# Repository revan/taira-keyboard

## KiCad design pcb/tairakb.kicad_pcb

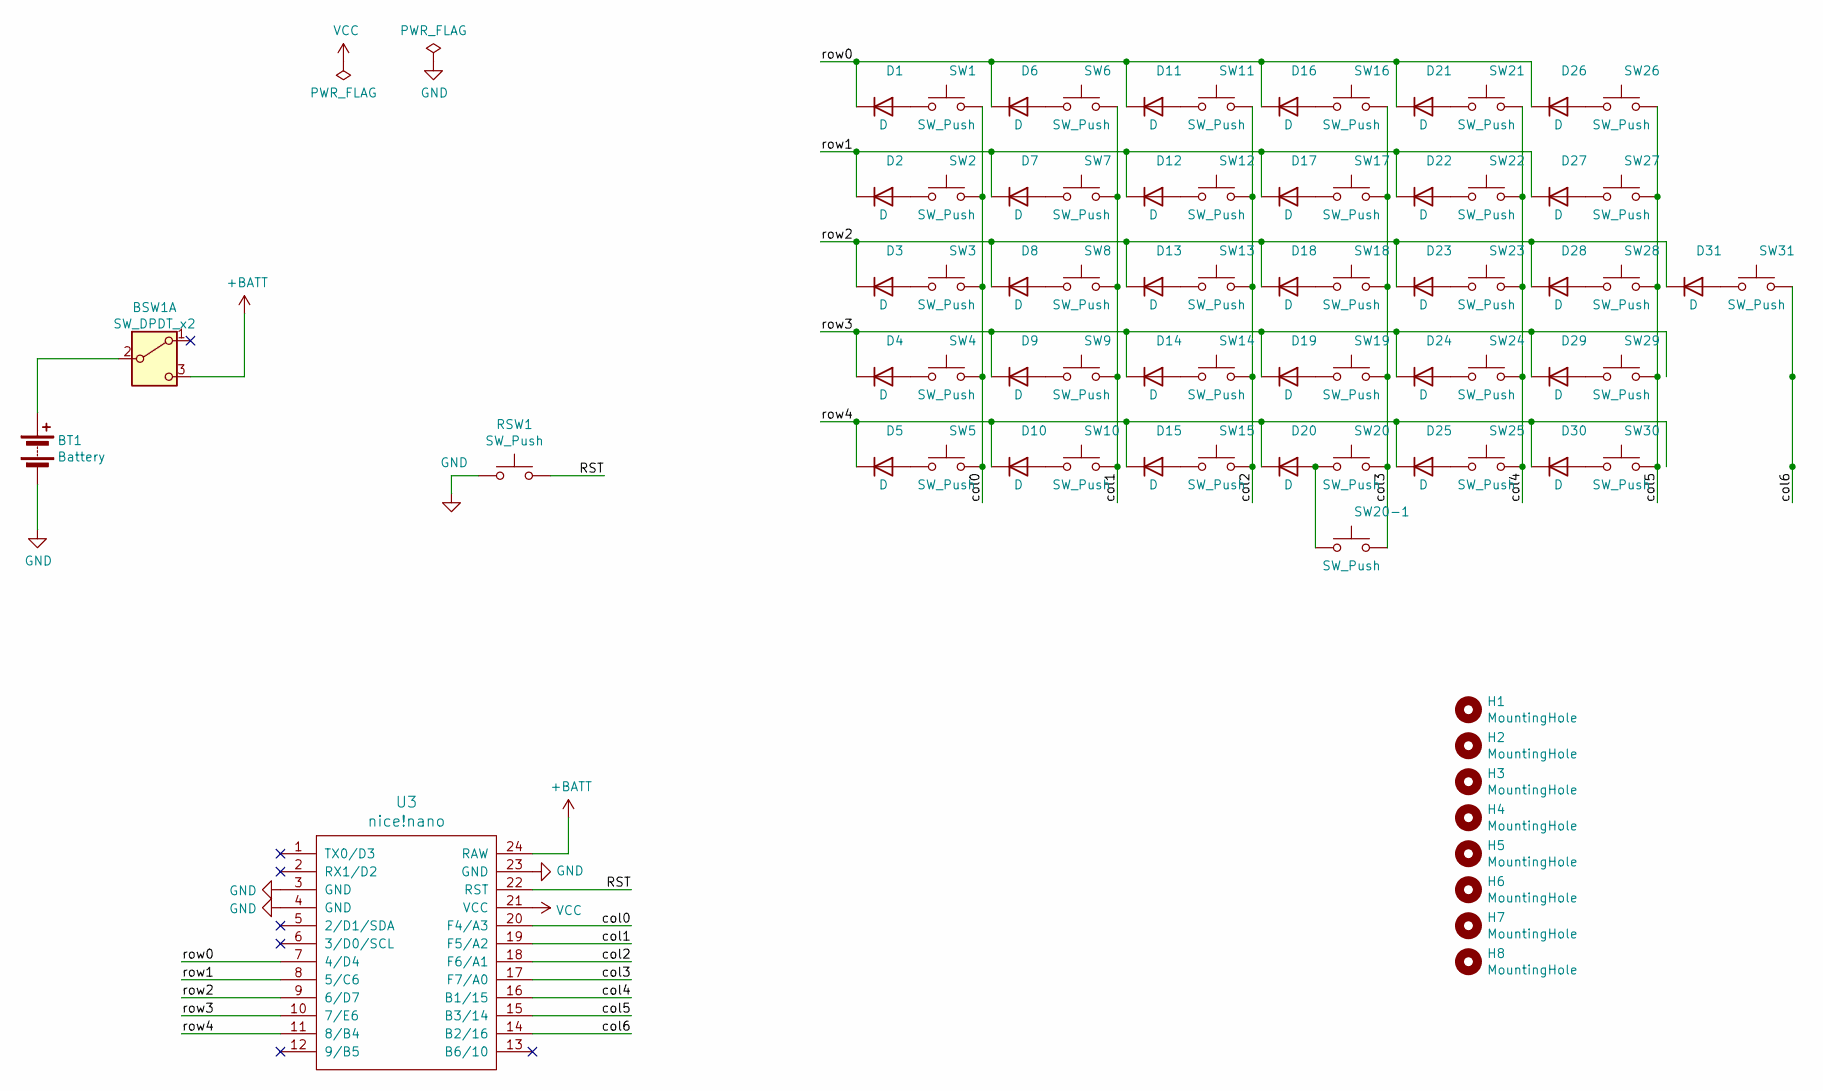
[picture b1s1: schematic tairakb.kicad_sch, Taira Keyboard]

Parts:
BSW1: SW_DPDT_x2; SS-12D00
BT1: Battery; Battery_Wire_Connector
D1, D2, D3, D4, D5, D6, D7, D8, D9, D10, D11, D12, D13, D14, D15, D16, D17, D18, D19, D20, D21, D22, D23, D24, D25, D26, D27, D28, D29, D30, D31: D; D3_SMD
H1, H2, H3, H4, H5, H6, H7, H8: MountingHole; LEGO_HOLE
RSW1: SW_Push; ResetSW
SW1, SW2, SW3, SW4, SW5, SW6, SW7, SW8, SW9, SW10, SW11, SW12, SW13, SW14, SW15, SW16, SW17, SW18, SW19, SW20, SW20-1, SW21, SW22, SW23, SW24, SW25, SW26, SW27, SW28, SW29, SW31: SW_Push; Choc_Hotswap
SW30: SW_Push; Choc_Hotswap_1.5U
U3: nice!nano; nicenano

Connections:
+BATT: BSW1.3 (C), U3.24 (RAW)
/RST: RSW1.2, U3.22 (RST)
/col0: SW1.2, SW2.2, SW3.2, SW4.2, SW5.2, U3.20 (F4/A3)
/col1: SW6.2, SW7.2, SW8.2, SW9.2, SW10.2, U3.19 (F5/A2)
/col2: SW11.2, SW12.2, SW13.2, SW14.2, SW15.2, U3.18 (F6/A1)
/col3: SW16.2, SW17.2, SW18.2, SW19.2, SW20.2, SW20-1.2, U3.17 (F7/A0)
/col4: SW21.2, SW22.2, SW23.2, SW24.2, SW25.2, U3.16 (B1/15)
/col5: SW26.2, SW27.2, SW28.2, SW29.2, SW30.2, U3.15 (B3/14)
/col6: SW31.2, U3.14 (B2/16)
/row0: D1.1 (K), D6.1 (K), D11.1 (K), D16.1 (K), D21.1 (K), D26.1 (K), U3.7 (4/D4)
/row1: D2.1 (K), D7.1 (K), D12.1 (K), D17.1 (K), D22.1 (K), D27.1 (K), U3.8 (5/C6)
/row2: D3.1 (K), D8.1 (K), D13.1 (K), D18.1 (K), D23.1 (K), D28.1 (K), D31.1 (K), U3.9 (6/D7)
/row3: D4.1 (K), D9.1 (K), D14.1 (K), D19.1 (K), D24.1 (K), D29.1 (K), U3.10 (7/E6)
/row4: D5.1 (K), D10.1 (K), D15.1 (K), D20.1 (K), D25.1 (K), D30.1 (K), U3.11 (8/B4)
GND: BT1.2 (-), RSW1.1, U3.3 (GND), U3.4 (GND), U3.23 (GND)
unnamed: BSW1.2 (B), BT1.1 (+)
unnamed: D1.2 (A), SW1.1
unnamed: D2.2 (A), SW2.1
unnamed: D3.2 (A), SW3.1
unnamed: D4.2 (A), SW4.1
unnamed: D5.2 (A), SW5.1
unnamed: D6.2 (A), SW6.1
unnamed: D7.2 (A), SW7.1
unnamed: D8.2 (A), SW8.1
unnamed: D9.2 (A), SW9.1
unnamed: D10.2 (A), SW10.1
unnamed: D11.2 (A), SW11.1
unnamed: D12.2 (A), SW12.1
unnamed: D13.2 (A), SW13.1
unnamed: D14.2 (A), SW14.1
unnamed: D15.2 (A), SW15.1
unnamed: D16.2 (A), SW16.1
unnamed: D17.2 (A), SW17.1
unnamed: D18.2 (A), SW18.1
unnamed: D19.2 (A), SW19.1
unnamed: D20.2 (A), SW20.1, SW20-1.1
unnamed: D21.2 (A), SW21.1
unnamed: D22.2 (A), SW22.1
unnamed: D23.2 (A), SW23.1
unnamed: D24.2 (A), SW24.1
unnamed: D25.2 (A), SW25.1
unnamed: D26.2 (A), SW26.1
unnamed: D27.2 (A), SW27.1
unnamed: D28.2 (A), SW28.1
unnamed: D29.2 (A), SW29.1
unnamed: D30.2 (A), SW30.1
unnamed: D31.2 (A), SW31.1
VCC: U3.21 (VCC)

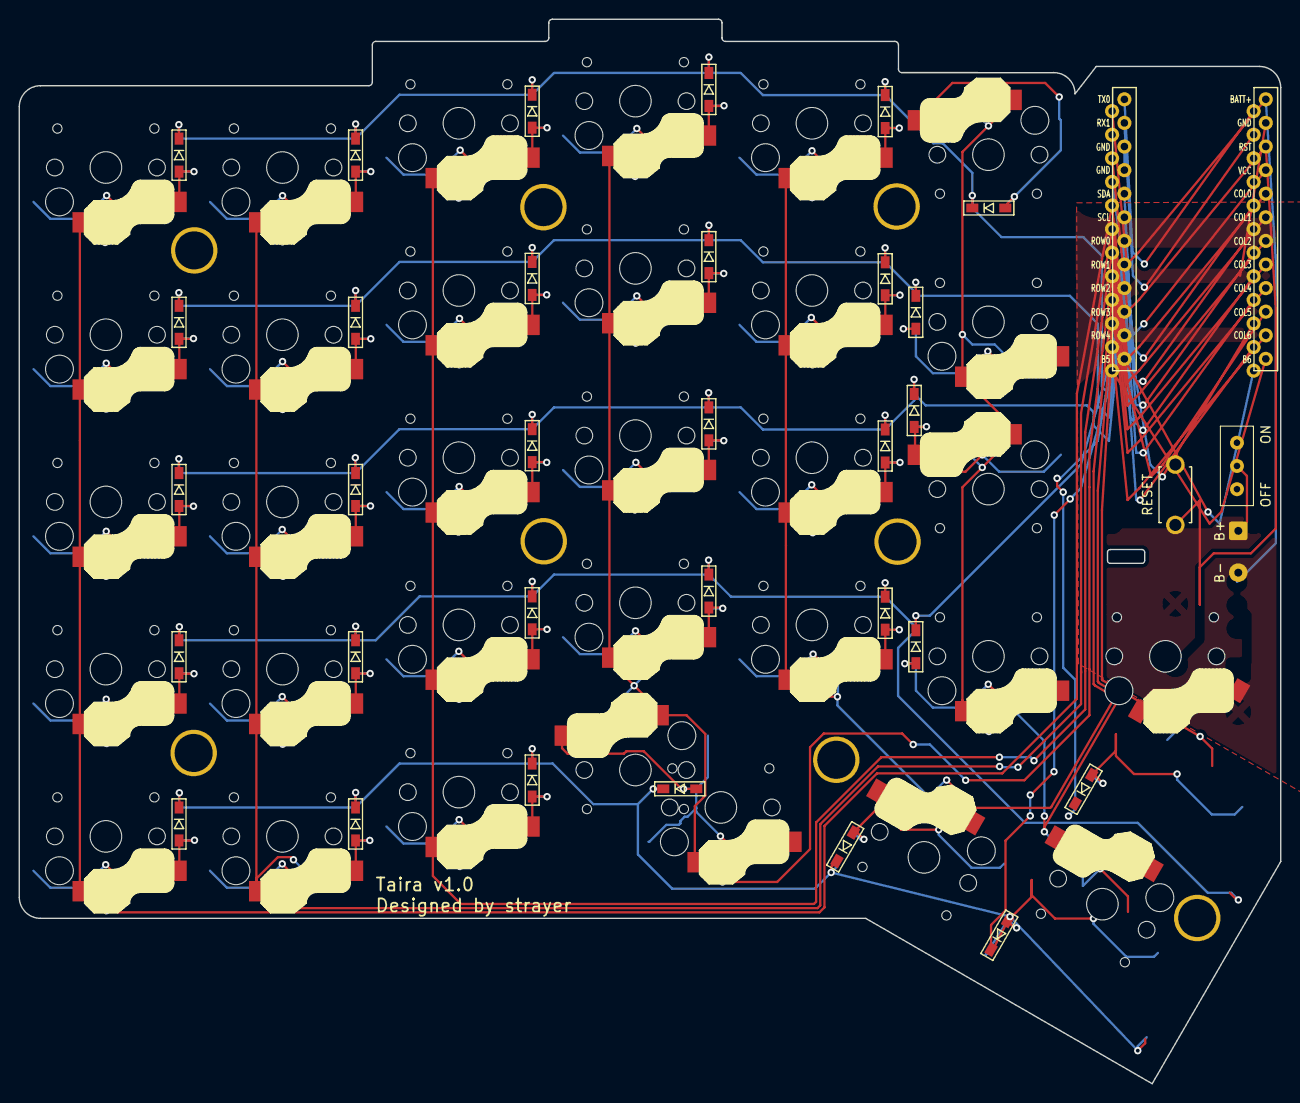
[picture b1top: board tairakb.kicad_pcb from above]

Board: 2 copper layers, 135.8 x 114.6 mm, 75 parts (0 on the bottom side), 47 nets.

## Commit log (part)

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2026-05-18 kicad 4 -> 10
2026-05-18 build script

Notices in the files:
pcb/tairakb.kicad_pcb:
Licensed under the MIT License - Copyright (c) 2021 Sven Grunewaldt
parts and their libraries:
Licensed under the MIT License - Copyright (c) 2019 foostan - Based on https://github.com/foostan/crkbd/tree/main/corne-chocolate/pcb
Mini power slide switch – Licensed under CC-BY-SA-4.0 (based on https://github.com/kaibader/KiCad-Library)
